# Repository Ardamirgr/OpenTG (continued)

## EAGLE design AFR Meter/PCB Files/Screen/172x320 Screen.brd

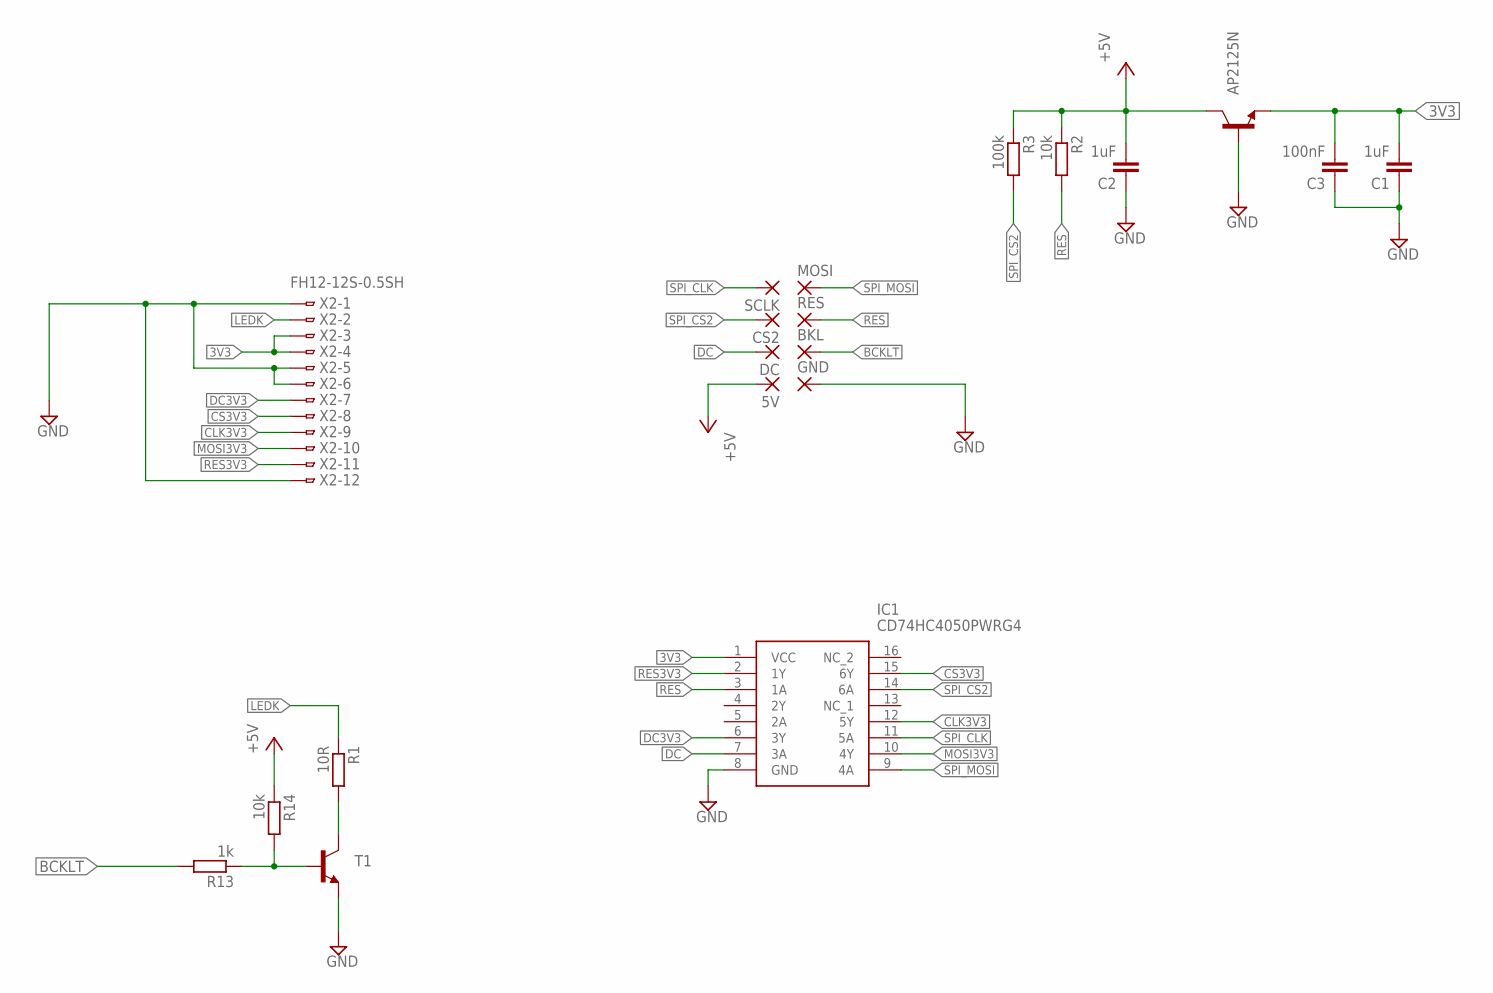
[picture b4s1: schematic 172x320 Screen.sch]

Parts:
5V: 1,6/0,9
AP2125N: BC817-16-NPN-SOT23-BEC; SOT23-BEC
BKL: 1,6/0,9
C1, C2: 1uF; C0805
C3: 100nF; C0805
CS2: 1,6/0,9
DC: 1,6/0,9
GND: 1,6/0,9
IC1: CD74HC4050PWRG4; SOP65P640X120-16N
MOSI: 1,6/0,9
R1: 10R; R0805
R2, R14: 10k; R0805
R3: 100k; R0805
R13: 1k; R0805
RES: 1,6/0,9
SCLK: 1,6/0,9
T1: BC817-16-NPN-SOT23-BEC; SOT23-BEC
X2: FH12-12S-0.5SH

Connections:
3V3: AP2125N.E, C1.2, C3.2, IC1.1 (VCC), X2.3, X2.4
+5V: 5V.1, AP2125N.C, C2.2, R2.1, R3.1, R14.1
BCKLT: BKL.1, R13.2
CLK3V3: IC1.12 (5Y), X2.9
CS3V3: IC1.15 (6Y), X2.8
DC: DC.1, IC1.7 (3A)
DC3V3: IC1.6 (3Y), X2.7
GND: AP2125N.B, C1.1, C2.1, C3.1, GND.1, IC1.8 (GND), T1.E, X2.1, X2.5, X2.6, X2.12
LEDK: R1.1, X2.2
MOSI3V3: IC1.10 (4Y), X2.10
unnamed: R1.2, T1.C
unnamed: R13.1, R14.2, T1.B
RES: IC1.3 (1A), R2.2, RES.1
RES3V3: IC1.2 (1Y), X2.11
SPI_CLK: IC1.11 (5A), SCLK.1
SPI_CS2: CS2.1, IC1.14 (6A), R3.2
SPI_MOSI: IC1.9 (4A), MOSI.1

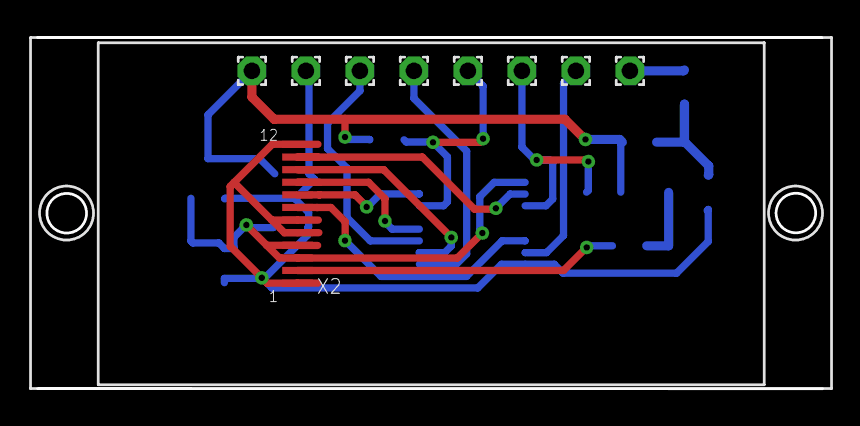
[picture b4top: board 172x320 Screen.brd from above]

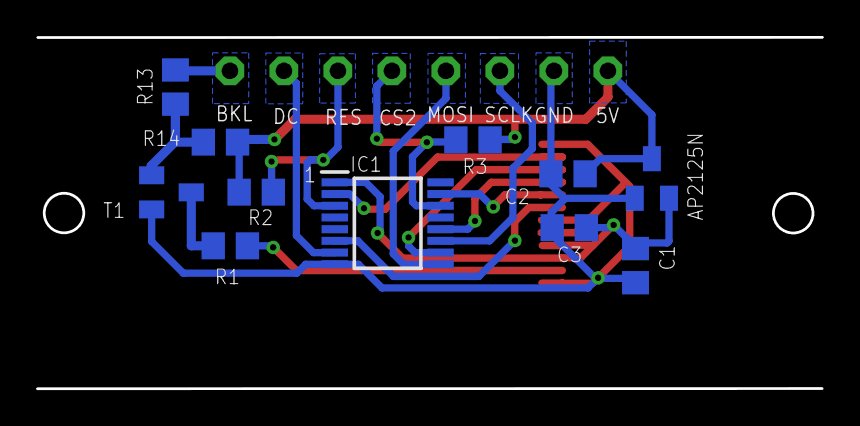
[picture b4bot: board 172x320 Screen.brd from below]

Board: 2 copper layers, 43.6 x 19.5 mm, 20 parts (11 on the bottom side), 17 nets.

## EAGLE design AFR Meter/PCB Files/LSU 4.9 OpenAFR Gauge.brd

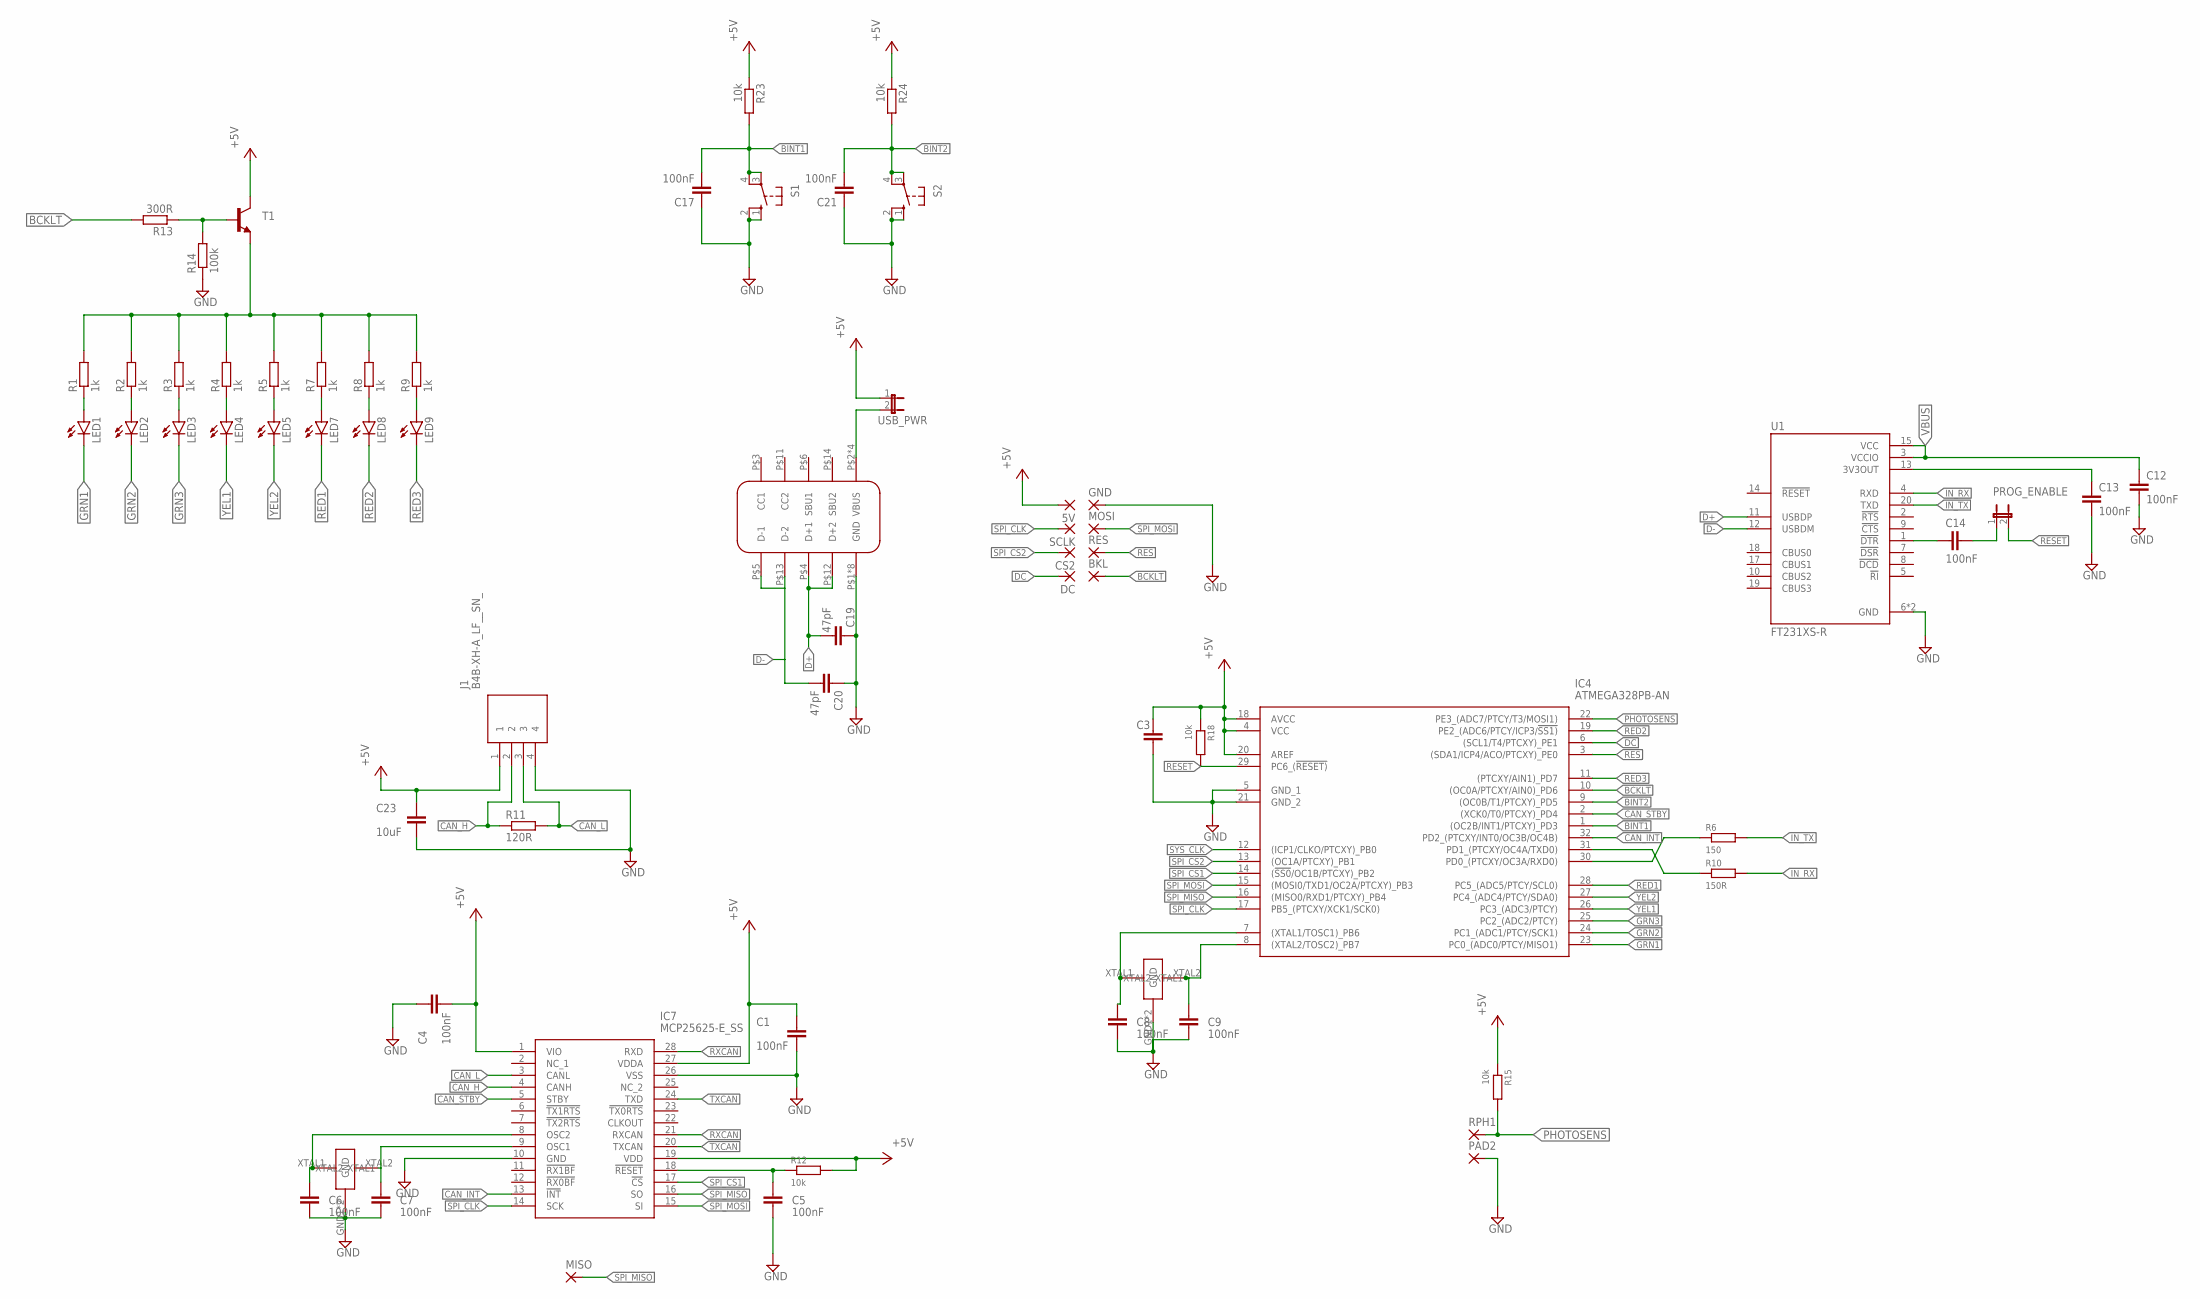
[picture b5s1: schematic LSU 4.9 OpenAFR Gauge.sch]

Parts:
5V: 1,6/0,9
BKL: 1,6/0,9
C1, C3, C4, C5, C6, C7, C8, C9, C12, C13, C14, C17, C21: 100nF; C0805
C19, C20: 47pF; C0805
C23: 10uF; C0805
CS2: 1,6/0,9
DC: 1,6/0,9
GND: 1,6/0,9
IC4: ATMEGA328PB-AN; QFP80P900X900X120-32N
IC7: MCP25625-E_SS; SOP65P780X200-28N
J1: B4B-XH-A_LF__SN_; B4BXHALFSN
LED1, LED2, LED3, LED4, LED5, LED7, LED8, LED9: LEDCHIPLED_1206; CHIPLED_1206
MISO: 1,6/0,9
MOSI: 1,6/0,9
PAD2: 1,6/0,8
PROG_ENABLE: JP1E; JP1
R1, R2, R3, R4, R5, R7, R8, R9: 1k; R0805
R6: 150; R0805
R10: 150R; R0805
R11: 120R; R1206
R12, R15, R18, R23, R24: 10k; R0805
R13: 300R; R0805
R14: 100k; R0805
RES: 1,6/0,9
RPH1: 1,6/0,8
S1, S2: 10-XX; B3F-10XX
SCLK: 1,6/0,9
T1: BC817-16-NPN-SOT23-BEC; SOT23-BEC
U1: FT231XS-R; SOP63P599X175-20N
U$1: USBC-2.0-THT
U$2, U$3: E3X160181X04
USB_PWR: JP1E; JP1

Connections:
+5V: 5V.1, C1.1, C3.1, C4.2, C23.1, IC4.4 (VCC), IC4.18 (AVCC), IC4.20 (AREF), IC7.1 (VIO), IC7.19 (VDD), IC7.27 (VDDA), J1.1, R12.2, R15.1, R18.1, R23.1, R24.1, T1.C, USB_PWR.1
BCKLT: BKL.1, IC4.10 ((OC0A/PTCXY/AIN0)_PD6), R13.2
BINT1: C17.2, IC4.1 ((OC2B/INT1/PTCXY)_PD3), R23.2, S1.3, S1.4 (P1)
BINT2: C21.2, IC4.9 ((OC0B/T1/PTCXY)_PD5), R24.2, S2.3, S2.4 (P1)
CAN_H: IC7.4 (CANH), J1.2, R11.1
CAN_INT: IC4.32 (PD2_(PTCXY/INT0/OC3B/OC4B)), IC7.13 (!INT)
CAN_L: IC7.3 (CANL), J1.3, R11.2
CAN_STBY: IC4.2 ((XCK0/T0/PTCXY)_PD4), IC7.5 (STBY)
D+: C19.2, U1.11 (USBDP), U$1.P$4 (D+1), U$1.P$12 (D+2)
D-: C20.2, U1.12 (USBDM), U$1.P$5 (D-1), U$1.P$13 (D-2)
DC: DC.1, IC4.6 ((SCL1/T4/PTCXY)_PE1)
GND: C1.2, C3.2, C4.1, C5.2, C6.2, C7.2, C8.2, C9.2, C12.2, C13.2, C17.1, C19.1, C20.1, C21.1, C23.2, GND.1, IC4.5 (GND_1), IC4.21 (GND_2), IC7.10 (GND), IC7.26 (VSS), J1.4, PAD2.1, R14.1, S1.1 (S), S1.2 (S1), S2.1 (S), S2.2 (S1), U1.6 (GND), U1.16 (GND), U$1.P$1 (GND), U$1.P$8 (GND), U$1.P$9 (GND), U$1.P$16 (GND), U$1.P$17 (GND), U$1.P$18 (GND), U$1.P$19 (GND), U$1.P$20 (GND), U$2.GND1 (GND), U$2.GND2 (GND), U$3.GND1 (GND), U$3.GND2 (GND)
GRN1: IC4.23 (PC0_(ADC0/PTCY/MISO1)), LED1.C
GRN2: IC4.24 (PC1_(ADC1/PTCY/SCK1)), LED2.C
GRN3: IC4.25 (PC2_(ADC2/PTCY)), LED3.C
IN_RX: R10.2, U1.4 (RXD)
IN_TX: R6.2, U1.20 (TXD)
unnamed: LED1.A, R1.1
unnamed: IC4.30 (PD0_(PTCXY/OC3A/RXD0)), R6.1
unnamed: LED2.A, R2.1
unnamed: LED3.A, R3.1
unnamed: LED4.A, R4.1
unnamed: LED5.A, R5.1
unnamed: IC4.31 (PD1_(PTCXY/OC4A/TXD0)), R10.1
unnamed: LED7.A, R7.1
unnamed: LED8.A, R8.1
unnamed: LED9.A, R9.1
unnamed: C7.1, IC7.9 (OSC1), U$2.XTAL2
unnamed: C6.1, IC7.8 (OSC2), U$2.XTAL1
unnamed: C5.1, IC7.18 (!RESET), R12.1
unnamed: C9.1, IC4.8 ((XTAL2/TOSC2)_PB7), U$3.XTAL2
unnamed: R1.2, R2.2, R3.2, R4.2, R5.2, R7.2, R8.2, R9.2, T1.E
unnamed: R13.1, R14.2, T1.B
unnamed: C14.2, PROG_ENABLE.1
unnamed: C13.1, U1.13 (3V3OUT)
unnamed: C14.1, U1.1 (!DTR)
unnamed: C8.1, IC4.7 ((XTAL1/TOSC1)_PB6), U$3.XTAL1
PHOTOSENS: IC4.22 (PE3_(ADC7/PTCY/T3/MOSI1)), R15.2, RPH1.1
RED1: IC4.28 (PC5_(ADC5/PTCY/SCL0)), LED7.C
RED2: IC4.19 (PE2_(ADC6/PTCY/ICP3/!SS1)), LED8.C
RED3: IC4.11 ((PTCXY/AIN1)_PD7), LED9.C
RES: IC4.3 ((SDA1/ICP4/ACO/PTCXY)_PE0), RES.1
RESET: IC4.29 (PC6_(!RESET)), PROG_ENABLE.2, R18.2
RXCAN: IC7.21 (RXCAN), IC7.28 (RXD)
SPI_CLK: IC4.17 (PB5_(PTCXY/XCK1/SCK0)), IC7.14 (SCK), SCLK.1
SPI_CS1: IC4.14 ((!SS0!/OC1B/PTCXY)_PB2), IC7.17 (!CS)
SPI_CS2: CS2.1, IC4.13 ((OC1A/PTCXY)_PB1)
SPI_MISO: IC4.16 ((MISO0/RXD1/PTCXY)_PB4), IC7.16 (SO), MISO.1
SPI_MOSI: IC4.15 ((MOSI0/TXD1/OC2A/PTCXY)_PB3), IC7.15 (SI), MOSI.1
SYS_CLK: IC4.12 ((ICP1/CLKO/PTCXY)_PB0)
TXCAN: IC7.20 (TXCAN), IC7.24 (TXD)
VBUS: C12.1, U1.3 (VCCIO), U1.15 (VCC), U$1.P$2 (VBUS), U$1.P$7 (VBUS), U$1.P$10 (VBUS), U$1.P$15 (VBUS), USB_PWR.2
YEL1: IC4.26 (PC3_(ADC3/PTCY)), LED4.C
YEL2: IC4.27 (PC4_(ADC4/PTCY/SDA0)), LED5.C

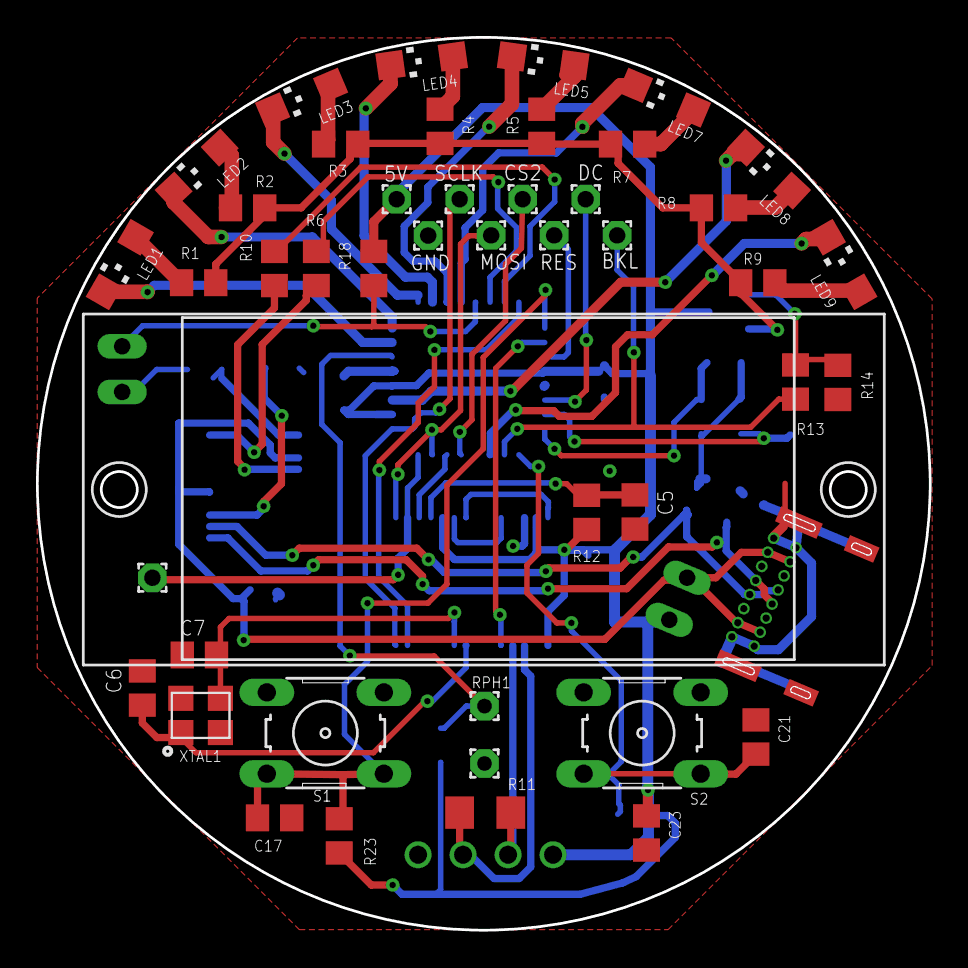
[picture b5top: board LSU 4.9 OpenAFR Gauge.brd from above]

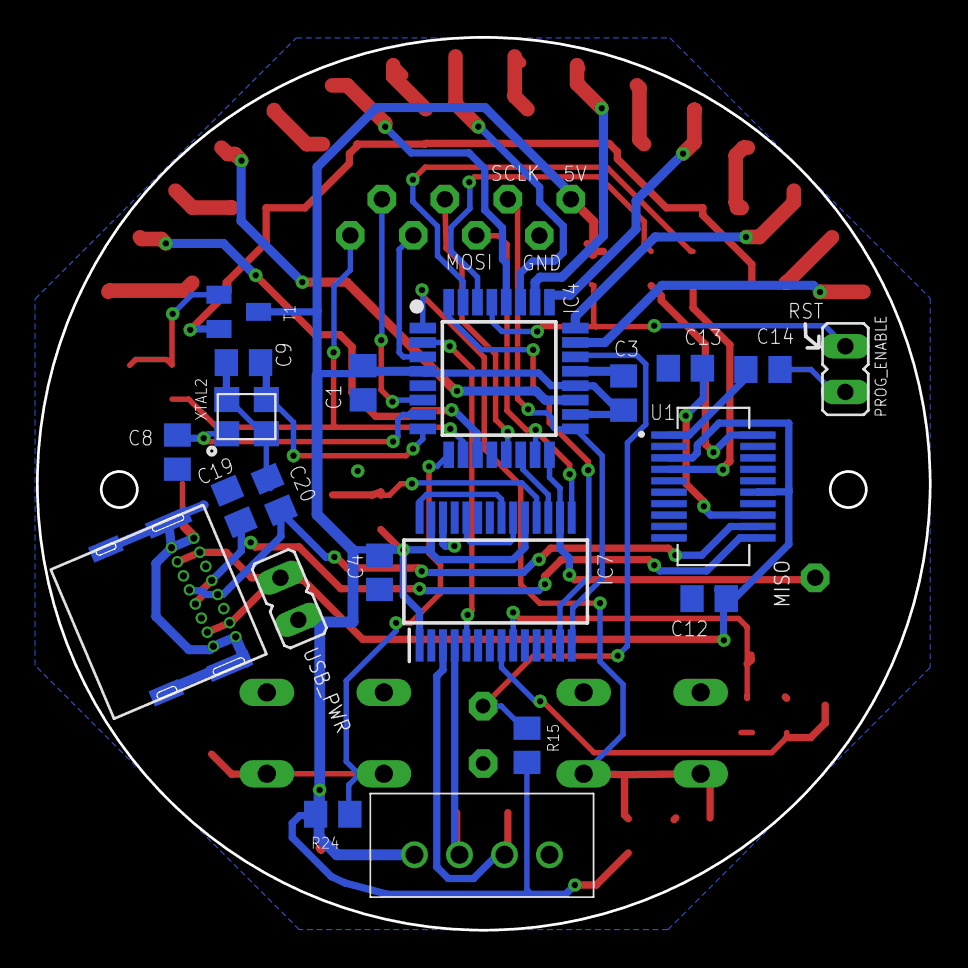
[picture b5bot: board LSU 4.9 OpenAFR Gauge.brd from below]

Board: 2 copper layers, 49.6 x 49.6 mm, 65 parts (21 on the bottom side), 53 nets.

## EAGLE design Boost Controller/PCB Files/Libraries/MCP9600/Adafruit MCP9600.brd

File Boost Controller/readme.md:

# Boost Controller

An open-source electronic boost controller for driving a MAC valve solenoid using closed-loop MAP feedback.

The controller supports boost-by-gear, boost-by-RPM, selectable boost profiles, CAN-based engine data, analog sensor inputs, EGT monitoring, and a companion gauge/display unit.

> [!WARNING]
> This project controls turbocharger boost pressure. Incorrect wiring, calibration, plumbing, or control behavior can cause overboost, lean operation, engine damage, turbocharger damage, drivetrain damage, or loss of traction. Bench-test the hardware first, start with low boost targets, and keep proper ECU-side overboost/fuel-cut protection enabled.

---

## Features

- Closed-loop boost control using MAP feedback
- MAC valve PWM control through MOSFET output
- Boost target by gear and RPM
- Up to 4 selectable boost profiles
- CAN-based RPM and vehicle speed input
- Optional analog RPM/VSS input support
- MAP sensor input
- Integrated IAT reading through MAP sensor NTC
- Type-K EGT reading using MCP9600
- CAN output for external gauge/display
- Status and fault reporting
- Debug mode with serial output
- Companion gauge support for boost, EGT, IAT, status, active profile, and LED bar display

> [!NOTE]
> The firmware is structured in an ECU-like way: lookup tables, interpolation, scheduled tasks, fixed-point integer math, and status/fault flags instead of blocking control logic.

---

## System Overview

The Boost Controller reads engine and vehicle data, calculates a target boost level from calibration tables, and controls a MAC valve solenoid with a PWM-driven MOSFET.

```text
RPM / VSS / Gear / Profile
          |
          v
Boost target lookup table
          |
          v
Atmospheric pressure compensation
          |
          v
Closed-loop PI boost control
          |
          v
MAC valve PWM output
```

The controller is intended for custom turbocharged engine setups where flexible gear-dependent boost control is required.

---

## Hardware

The controller is designed around:

| Hardware | Purpose |
|---|---|
| ATmega328PB or similar AVR MCU | Main controller |
| MCP25625 | CAN controller/transceiver |
| MAC valve boost solenoid | Wastegate pressure control |
| Logic-level MOSFET | MAC valve low-side drive |
| MAP sensor with integrated IAT NTC | Boost and intake temperature measurement |
| MCP9600 | Type-K thermocouple interface |
| 5V logic supply | MCU and sensor logic |
| 12V automotive supply input | Vehicle power and solenoid supply |
| Companion gauge/display | User interface and live feedback |

### Main Inputs

| Input | Description |
|---|---|
| MAP | Manifold absolute pressure sensor |
| IAT | Integrated NTC inside the MAP sensor |
| EGT | Type-K thermocouple through MCP9600 |
| RPM | CAN or hardware timer input |
| VSS | CAN or hardware timer input |
| Profile Select | Received from dashboard/gauge over CAN |

### Main Outputs

| Output | Description |
|---|---|
| MAC PWM | 15–30 Hz PWM output for MAC valve |
| CAN TX | Sensor/status data sent to gauge |
| Status LEDs | Power and CAN status indication |

> [!IMPORTANT]
> Use proper automotive protection: fuse the supply, protect the MOSFET gate, use flyback suppression for the solenoid, and make sure the MAC valve plumbing fails to a safe mechanical wastegate pressure.

---

## Boost Control Strategy

Boost targets are stored as **gauge pressure in mbar**.

The controller captures atmospheric pressure at key-on and adds the selected boost target on top of it:

```c
target_map_abs = ambient_pressure + boost_target_gauge;
```

The PI controller compares this absolute target against the live MAP reading:

```c
error = target_map_abs - measured_map_abs;
```

The PI output then drives the MAC valve PWM duty cycle.

This keeps the boost tables intuitive while allowing the controller to operate using absolute pressure internally.

> [!TIP]
> Keep boost calibration tables in gauge mbar for easy tuning, but compare absolute pressure internally because the MAP sensor measures absolute manifold pressure.

---

## Boost Profiles

The firmware supports up to 4 boost profiles:

| Profile | Intended Use |
|---:|---|
| 0 | Mild / Economy |
| 1 | Street |
| 2 | Sport |
| 3 | Race / Maximum |

Each profile contains a gear/RPM boost target map:

```c
boost_profile[gear][rpm_point]
```

The RPM axis is shared across all profiles and boost targets are interpolated between breakpoints.

> [!NOTE]
> Boost map values are gauge pressure values. The controller adds the stored ambient pressure to create the final absolute MAP target.

---

## Scheduler

The firmware uses a Timer2-based cooperative scheduler with a 5 ms base tick.

Typical task timing:

| Task | Interval |
|---|---:|
| MAP read | 10 ms |
| RPM/VSS read | 10 ms |
| Boost control | 40 ms |
| CAN transmit | 100 ms |
| IAT read | 200 ms |
| EGT / ambient read | 500 ms |

The MAC valve PWM itself is generated separately by Timer1.

> [!NOTE]
> The boost PI routine is intentionally slower than the ADC sampling. Sensor values are refreshed first, then the 40 ms boost-control task uses the latest cached values.

---

## MAC Valve PWM

The MAC valve is driven using Timer1 PWM.

Default configuration:

| Parameter | Value |
|---|---:|
| PWM frequency | 25 Hz |
| Output | Timer1 OC1A |
| Duty command range | 0–255 |

The firmware can compensate for the usable MAC valve duty range. For example, if the valve is non-responsive below `20/255` and fully open above `215/255`, the logical 0–255 control output can be mapped into the effective valve range.

> [!CAUTION]
> Forced PWM test patterns should only be run on the bench or with boost-control plumbing safely disconnected. Do not sweep the MAC valve duty on a live boost system unless you know exactly how the plumbing will respond.

---

## CAN Communication

The controller receives RPM and vehicle speed data from the ECU when CAN sensor mode is enabled.

It also transmits live data to the companion gauge.

### Controller-to-Gauge CAN Frame

| Byte | Data |
|---:|---|
| 0 | Status flags |
| 1–2 | MAP absolute pressure, mbar |
| 3–4 | EGT, °C |
| 5–6 | IAT, °C × 10 |
| 7 | Profile max boost, encoded as `max_boost * 100 mbar` |

Example:

```c
byte7 = 30; // 3000 mbar max boost
```

The gauge uses the profile max boost value to scale the LED bar and determine display warning colors.

> [!IMPORTANT]
> CAN-derived RPM/VSS data is timeout-protected. If ECU CAN messages stop arriving, the controller invalidates RPM and VSS instead of continuing to use stale values.

---

## Gauge Display

The companion gauge can display:

- Boost in bar
- Boost in PSI
- EGT in °C
- IAT
- Status flags
- Active boost profile
- LED boost bar

The LED bar uses the profile max boost value for scaling.

Recommended behavior:

| Condition | LED / Display Behavior |
|---|---|
| Below max boost | Green display, normal LED scaling |
| At max boost | Yellow display / yellow LED |
| Over max boost | Red display / red LED |

> [!NOTE]
> The last two LEDs are intended as warning indicators: yellow for reaching the profile maximum and red for exceeding it.

---

## Status Flags

The firmware uses an 8-bit status register for reporting controller state and faults.

Example status layout:

```c
#define STATUS_DEBUG          (1 << 7)
#define STATUS_ENGINE_ON      (1 << 6)
#define STATUS_CAN_ACTIVE     (1 << 5)
#define STATUS_BOOST_ACTIVE   (1 << 4)
#define STATUS_EGT_FAIL       (1 << 3)
#define STATUS_MAP_FAULT      (1 << 2)
#define STATUS_VSS_FAULT      (1 << 1)
#define STATUS_LOW_BAT        (1 << 0)
```

These flags are transmitted over CAN and can be displayed by the gauge.

> [!TIP]
> Keep status bits specific. Avoid vague flags like `NORMAL` when possible; it is usually better to report the exact fault or active state.

---

## CAN Timeout Handling

When CAN-based RPM/VSS is used, the firmware tracks message freshness.

If ECU CAN messages stop arriving, RPM and VSS are invalidated after a timeout. This prevents the controller from continuing to use stale data.

Typical timeout:

```c
#define CAN_TIMEOUT_TICKS 20
```

With a 5 ms scheduler tick, this gives a timeout of approximately 100 ms.

When the timeout expires:

- RPM returns 0
- VSS returns 0
- Gear detection returns neutral/unknown
- Boost control is disabled by RPM threshold
- Fault/status bits can be set

> [!WARNING]
> Stale RPM or VSS data can cause unsafe boost control decisions. Timeout handling should remain enabled when CAN sensor mode is used.

---

## Sensors

### MAP Sensor

The MAP sensor is read through the ADC and converted to pressure using a lookup table.

The MAP reading is treated as absolute pressure in mbar.

### IAT Sensor

The IAT is an NTC integrated into the MAP sensor.

The firmware uses an ECU-style 1D lookup table:

```c
ADC axis -> temperature
```

Temperature is represented as `°C × 10`.

Example:

```c
253  =  25.3 °C
-100 = -10.0 °C
```

### EGT Sensor

EGT is measured using a Type-K thermocouple and the MCP9600.

The MCP9600 is used to read:

- Thermocouple temperature
- Board/ambient temperature

EGT is mainly used for display and warning/alert functionality.

> [!CAUTION]
> Sensor calibration is critical. Validate raw ADC values and converted values before enabling closed-loop boost control.

---

## Gear Detection

When gear is not directly received from CAN, the controller estimates gear from RPM and vehicle speed.

The basic relationship is:

```c
ratio = rpm / vss;
```

The calculated ratio is compared against calibrated expected values for each gear.

If no valid gear is detected, the controller returns gear `0`, meaning neutral, clutch-in, shifting, or invalid state.

> [!NOTE]
> Unknown gear returns a zero boost target. This prevents boost control during shifts, clutch-in conditions, or implausible RPM/VSS combinations.

---

## Safety Behavior

The firmware includes several safety-oriented behaviors:

- Boost control disabled below minimum RPM
- MAC valve output forced to zero when RPM is too low
- CAN timeout protection
- Unknown gear returns zero boost target
- Low battery flag support
- MAP/IAT plausibility checks can be added
- EGT failure and alert support
- Optional MAC valve response monitoring

> [!WARNING]
> Software boost control should never be the only safety layer. Use a safe mechanical wastegate spring, correct boost plumbing, proper overboost protection, and conservative initial calibration.

---

## Debug Mode

The firmware includes a debug mode that can output live data over serial.

Typical debug output includes:

- MAP
- IAT
- RPM
- VSS
- Gear
- Boost target
- MAC PWM duty
- EGT
- Ambient temperature
- Battery voltage
- CAN age
- Status flags

Debug mode can also step the MAC valve PWM output through a test pattern:

```text
0%, 20%, 40%, 60%, 80%, 0%
```

This is useful for bench-testing the MOSFET driver and valve output.

> [!CAUTION]
> Do not run forced PWM debug patterns on a live boost system unless the boost-control plumbing is safely disconnected.

---

## Development Notes

The project follows an ECU-style firmware structure:

- Calibration data stored in lookup tables
- Interpolation for sensor conversion and target lookup
- Scheduled periodic tasks
- Status flags for diagnostics
- CAN communication for external display
- Fixed-point integer math where practical

This keeps the firmware lightweight and suitable for AVR hardware.

---

## Installation / Bring-Up Checklist

> [!IMPORTANT]
> Validate the system in stages. Do not install the controller and immediately run high boost.

Recommended bring-up order:

1. Confirm 5V and 12V supplies.
2. Confirm CAN communication.
3. Confirm raw MAP and IAT ADC readings.
4. Confirm MAP and IAT conversion tables.
5. Confirm MCP9600 EGT and ambient readings.
6. Confirm Timer1 PWM frequency on a scope.
7. Confirm MOSFET gate and MAC valve output behavior.
8. Confirm RPM/VSS acquisition and gear detection.
9. Run with wastegate spring pressure only.
10. Enable low boost targets and gradually increase after logging.

---

## License

See the repository root for license information.

---

## Project Status

Work in progress.

Current development focus:

- Boost-by-gear and RPM control
- MAP/IAT calibration
- CAN RPM/VSS integration
- MCP9600 EGT support
- Gauge display integration
- MAC valve behavior testing
- Safety/fault handling

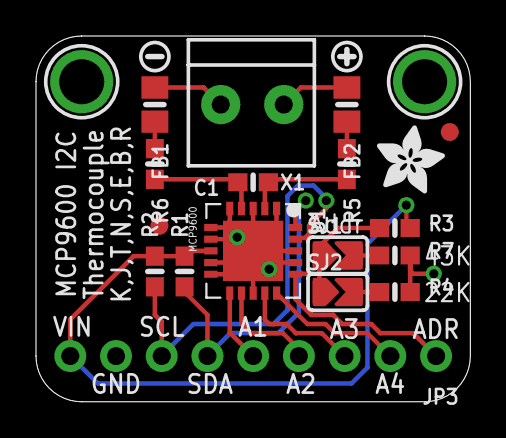
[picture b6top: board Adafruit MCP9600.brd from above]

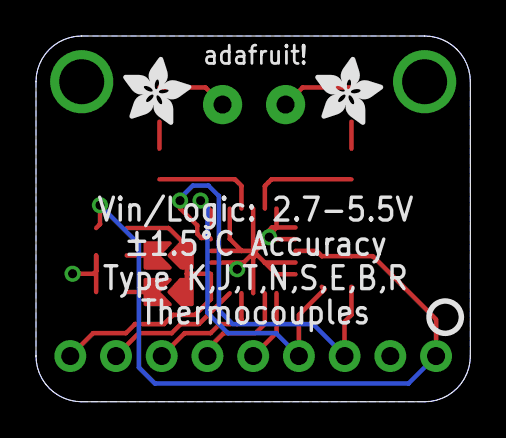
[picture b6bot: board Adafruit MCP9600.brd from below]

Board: 2 copper layers, 24.1 x 20.3 mm, 25 parts (3 on the bottom side), 17 nets.

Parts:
C1: 0.1uF; 0603-NO
FB1, FB2: Ferrite; 0805-NO
FID1, FID2: FIDUCIAL_1MM
JP3: 1X09_ROUND_70
R1, R2, R3: 10K; 0603-NO
R4: 22K; 0603-NO
R5, R6: 100; 0603-NO
R7: 47K; 0603-NO
SJ1, SJ2: SOLDERJUMPER_ARROW_NOPASTE
U1: MCP9600; VQFN20_5MM
U$1, U$3: MOUNTINGHOLE2.5; MOUNTINGHOLE_2.5_PLATED
U$16, U$19, U$20: ADAFRUIT_3.5MM
U$17: SYMBOL_PLUS
U$18: SYMBOL_MINUS
U$21: PCBFEAT-REV-040
X1: TERMBLK; TERMBLOCK_1X2-3.5MM

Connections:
+: FB2.1, X1.2
-: FB1.1, X1.1
ADDR: JP3.1, R3.1, SJ1.1, SJ2.1, U1.P$16
ALERT1: JP3.5, U1.P$11
ALERT2: JP3.4, U1.P$12
ALERT3: JP3.3, U1.P$14
ALERT4: JP3.2, U1.P$15
GND: JP3.8, R4.2, R7.2, U1.P$1, U1.P$3, U1.P$5, U1.P$6, U1.P$7, U1.P$9, U1.P$10, U1.P$13, U1.P$17, U1.P$18, U1.THRM
unnamed: C1.1, R5.2, U1.P$2
unnamed: C1.2, R6.2, U1.P$4
unnamed: FB1.2, R6.1
unnamed: FB2.2, R5.1
unnamed: R7.1, SJ1.2
unnamed: R4.1, SJ2.2
SCL: JP3.7, R2.1, U1.P$19
SDA: JP3.6, R1.1, U1.P$20
VIN: JP3.9, R1.2, R2.2, R3.2, U1.P$8

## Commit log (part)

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2026-01-24 Create Firmware
2026-01-24 Upload v1.0 and v1.1 (not yet finished) versions of firmware
2026-01-24 Add XBM icons used in the project
2026-01-24 Added PCB and schematic files
2026-01-24 Create foo
2026-02-03 Update PCBs to latest version
    Gauge:
    -- Changed FTDI 232RNL to FTDI 231XS (60% cheaper, smaller size, no need of extra features of the 232).
    -- Introduced gound plane to help with EMI immunity (noticed on buttons on very rare cases).
    -- Optimized capacitor placement and some trace routing.
    Mainboard:
    -- Introduced a proper DIP connector for programming.
2026-02-04 v0.1 PCB
2026-02-09 Fix upside down connector
2026-03-11 QoL changes for optimizing production
2026-03-11 Changed layout to include ground plane and some capacitors moved
2026-03-11 v0.2 PCB
2026-04-16 v0.1 firmware for Controller board
    Gauge is pre-alpha and an abandoned design choice. Will get to developing it after the controller board is confirmed working.
2026-04-19 v0.2 of the firmware, added gauge firmware
2026-04-19 Datasheets for sensors
2026-04-19 Python software for uploading profiles.
    No such function yet, will be added after the current controller has been tested and is working ok.
2026-04-19 V1.0 of the mainboard files
2026-05-02 Uploaded the files for the MAF adapter board
2026-06-03 48mm Gauge and Mainboard updates
2026-06-03 Mainboard power supply and QoL updates.
2026-06-03 Shrinked to 48.6mm for more space for the casing
2026-06-03 Small fixes v0.2
2026-06-05 Major updates for safe handling of boost control, sensors etc
2026-06-05 Name change
